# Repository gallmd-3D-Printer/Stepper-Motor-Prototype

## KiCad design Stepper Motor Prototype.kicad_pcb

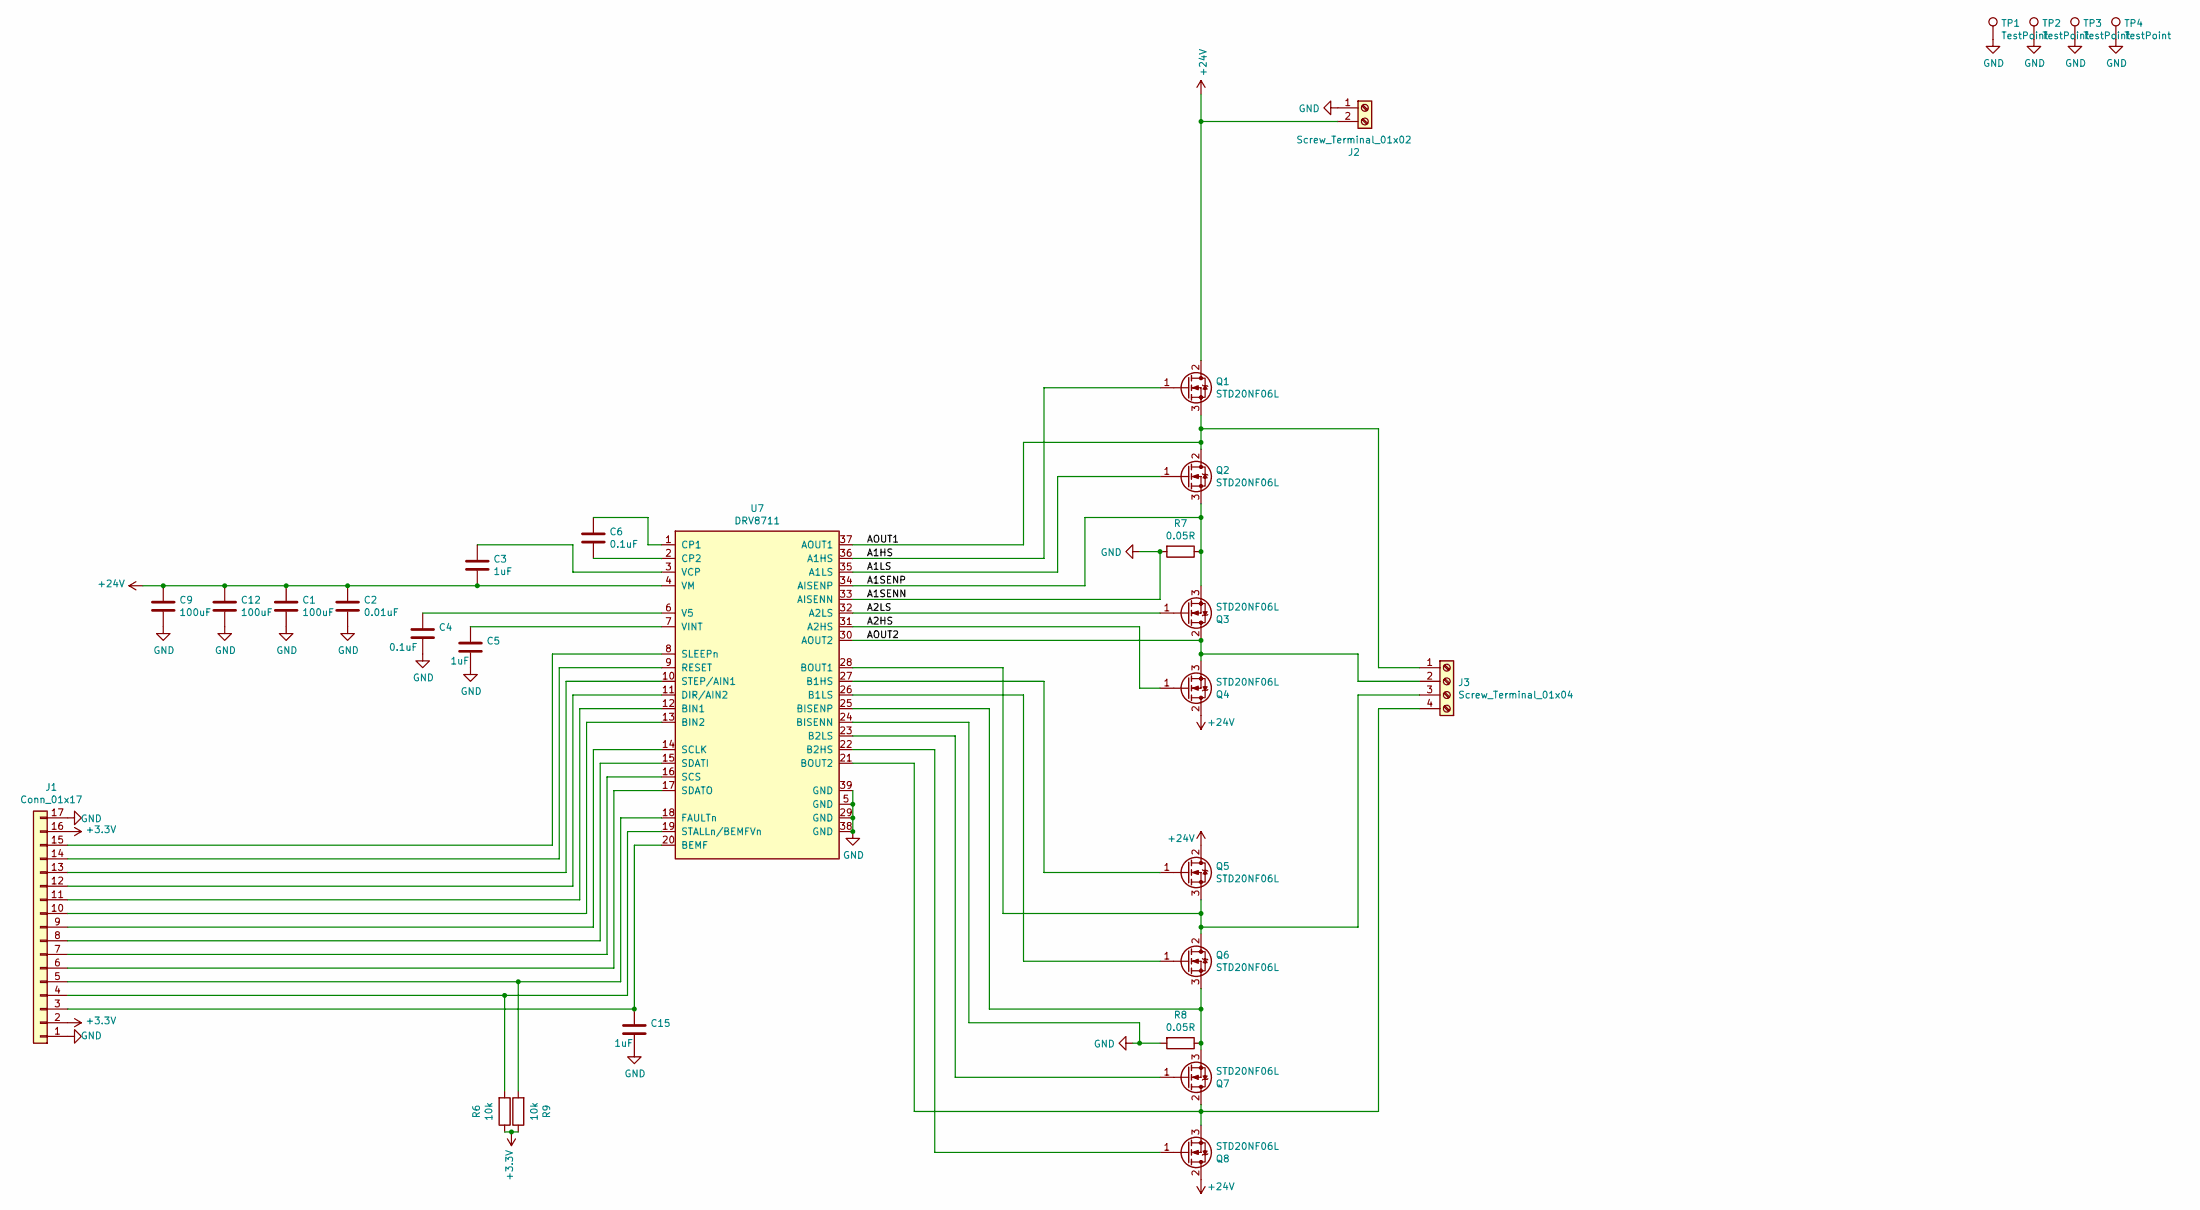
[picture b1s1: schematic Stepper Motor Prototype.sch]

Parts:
C1, C9, C12: 100uF; CP_Radial_D8.0mm_P3.50mm
C2: 0.01uF; C_0603_HandSoldering
C3, C5, C15: 1uF; C_0603_HandSoldering
C4, C6: 0.1uF; C_0603_HandSoldering
J1: Conn_01x17; Pin_Header_Straight_1x17_Pitch2.54mm
J2: Screw_Terminal_01x02; TerminalBlock_bornier-2_P5.08mm
J3: Screw_Terminal_01x04; TerminalBlock_bornier-4_P5.08mm
Q1, Q2, Q3, Q4, Q5, Q6, Q7, Q8: STD20NF06L; TO-252-2
R6, R9: 10k; R_0603_HandSoldering
R7, R8: 0.05R; R_2512
TP1, TP2, TP3, TP4: TestPoint; Test_Point_Keystone_5010-5014_Multipurpose
U7: DRV8711; TSSOP-38-1_PowerPad_4.4x9.7mm_Pitch0.5mm

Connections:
+3V3: J1.2, J1.16, R6.1, R9.1
+24V: C1.1, C2.1, C3.2, C9.1, C12.1, J2.2, Q1.2 (D), Q4.2 (D), Q5.2 (D), Q8.2 (D), U7.4 (VM)
/A1HS: Q1.1 (G), U7.36 (A1HS)
/A1LS: Q2.1 (G), U7.35 (A1LS)
/A1SENP: Q2.3 (S), Q3.3 (S), R7.1, U7.34 (AISENP)
/A2HS: Q4.1 (G), U7.31 (A2HS)
/A2LS: Q3.1 (G), U7.32 (A2LS)
/AOUT1: J3.1, Q1.3 (S), Q2.2 (D), U7.37 (AOUT1)
/AOUT2: J3.2, Q3.2 (D), Q4.3 (S), U7.30 (AOUT2)
GND: C1.2, C2.2, C4.2, C5.2, C9.2, C12.2, C15.2, J1.1, J1.17, J2.1, R7.2, R8.2, TP1.1, TP2.1, TP3.1, TP4.1, U7.5 (GND), U7.24 (BISENN), U7.29 (GND), U7.33 (AISENN), U7.38 (GND), U7.39 (GND)
unnamed: C3.1, U7.3 (VCP)
unnamed: C4.1, U7.6 (V5)
unnamed: C5.1, U7.7 (VINT)
unnamed: C6.1, U7.1 (CP1)
unnamed: C6.2, U7.2 (CP2)
unnamed: C15.1, J1.3, U7.20 (BEMF)
unnamed: J1.4, R6.2, U7.19 (STALLn/BEMFVn)
unnamed: J1.5, R9.2, U7.18 (FAULTn)
unnamed: J1.6, U7.17 (SDATO)
unnamed: J1.7, U7.16 (SCS)
unnamed: J1.8, U7.15 (SDATI)
unnamed: J1.9, U7.14 (SCLK)
unnamed: J1.10, U7.13 (BIN2)
unnamed: J1.11, U7.12 (BIN1)
unnamed: J1.12, U7.11 (DIR/AIN2)
unnamed: J1.13, U7.10 (STEP/AIN1)
unnamed: J1.14, U7.9 (RESET)
unnamed: J1.15, U7.8 (SLEEPn)
unnamed: J3.3, Q5.3 (S), Q6.2 (D), U7.28 (BOUT1)
unnamed: J3.4, Q7.2 (D), Q8.3 (S), U7.21 (BOUT2)
unnamed: Q5.1 (G), U7.27 (B1HS)
unnamed: Q6.1 (G), U7.26 (B1LS)
unnamed: Q6.3 (S), Q7.3 (S), R8.1, U7.25 (BISENP)
unnamed: Q7.1 (G), U7.23 (B2LS)
unnamed: Q8.1 (G), U7.22 (B2HS)

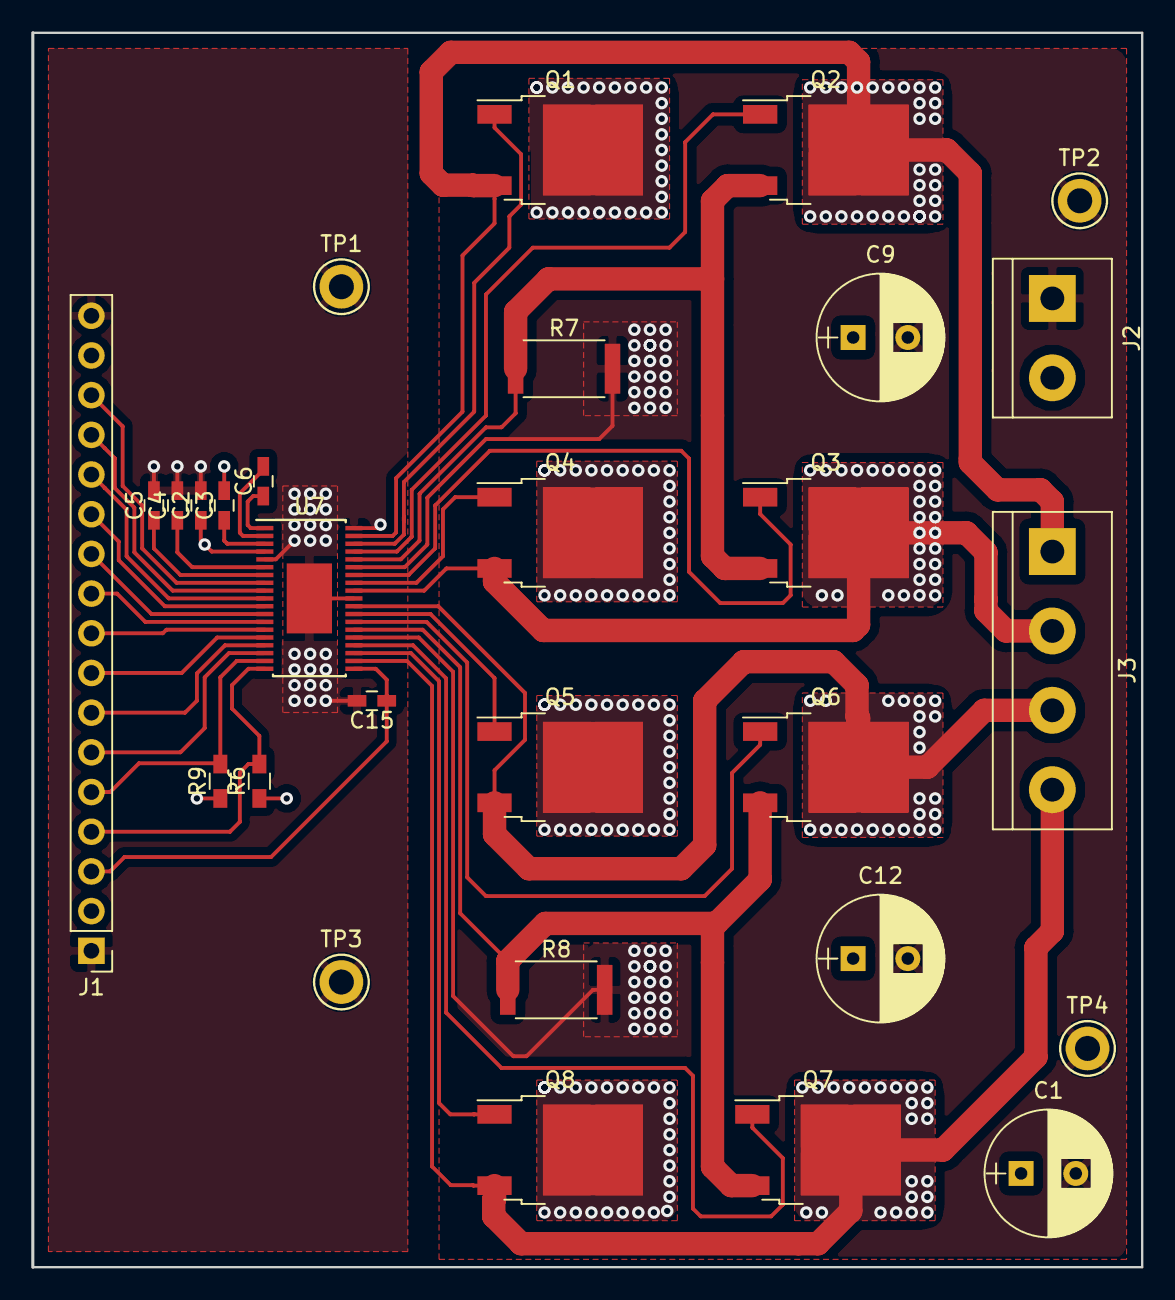
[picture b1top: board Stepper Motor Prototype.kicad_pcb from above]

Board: 4 copper layers, 71.0 x 79.0 mm, 29 parts (0 on the bottom side), 35 nets.

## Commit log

2019-02-09 ripped up whole board. Only power components and 1 stepper driver will be on this board
2019-02-23 added logic level shifters
2019-02-23 removed power supply, basic layout of 1 motor winding complete
2019-02-27 continued working on motor power section. Still need to layout mirrored side.
2019-02-28 finished laying out second side of motor power section
2019-03-02 traces are all connected, still need to refine routing of logic side
2019-03-05 removed voltage level translator, all nets are connected
